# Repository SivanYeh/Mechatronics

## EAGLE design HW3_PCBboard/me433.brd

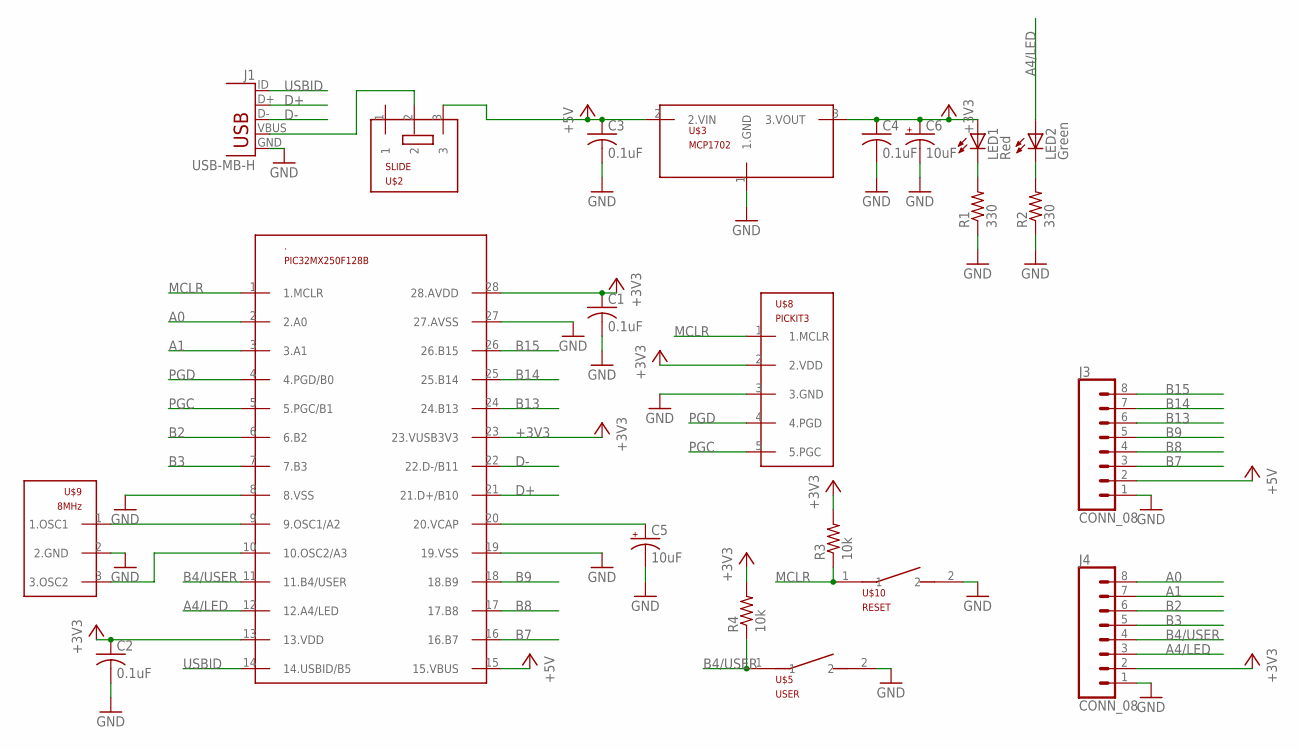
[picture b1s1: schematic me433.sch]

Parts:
.: PIC32MX250F128B; DIL28-3
C1, C2, C3, C4: 0.1uF; C025-025X050
C5, C6: 10uF; B45181B
J1: USB-MB-H
J3, J4: CONN_08; 1X08
LED1: Red; LED3MM
LED2: Green; LED3MM
R1, R2: 330; 0207/10
R3, R4: 10k; 0207/10
U$2: SLIDE
U$3: MCP1702; TO92
U$5: USER; PB
U$8: PICKIT3; 1X05
U$9: 8MHz; OSC
U$10: RESET; PB

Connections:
+3V3: ..13 (13.VDD), ..23 (23.VUSB3V3), ..28 (28.AVDD), C1.1, C2.1, C4.1, C6.+, J4.2, LED1.A, R3.2, R4.2, U$3.3 (3.VOUT), U$8.2 (2.VDD)
+5V: ..15 (15.VBUS), C3.1, J3.2, U$2.3, U$3.2 (2.VIN)
A0: ..2 (2.A0), J4.8
A1: ..3 (3.A1), J4.7
A4/LED: ..12 (12.A4/LED), J4.3, LED2.A
B2: ..6 (6.B2), J4.6
B3: ..7 (7.B3), J4.5
B4/USER: ..11 (11.B4/USER), J4.4, R4.1, U$5.1
B7: ..16 (16.B7), J3.3
B8: ..17 (17.B8), J3.4
B9: ..18 (18.B9), J3.5
B13: ..24 (24.B13), J3.6
B14: ..25 (25.B14), J3.7
B15: ..26 (26.B15), J3.8
D+: ..21 (21.D+/B10), J1.D+
D-: ..22 (22.D-/B11), J1.D-
GND: ..8 (8.VSS), ..19 (19.VSS), ..27 (27.AVSS), C1.2, C2.2, C3.2, C4.2, C5.-, C6.-, J1.GND, J3.1, J4.1, R1.1, R2.1, U$3.1 (1.GND), U$5.2, U$8.3 (3.GND), U$9.2 (2.GND), U$10.2
MCLR: ..1 (1.MCLR), R3.1, U$8.1 (1.MCLR), U$10.1
unnamed: LED2.K (C), R2.2
unnamed: ..9 (9.OSC1/A2), U$9.1 (1.OSC1)
unnamed: ..10 (10.OSC2/A3), U$9.3 (3.OSC2)
unnamed: LED1.K (C), R1.2
unnamed: ..20 (20.VCAP), C5.+
PGC: ..5 (5.PGC/B1), U$8.5 (5.PGC)
PGD: ..4 (4.PGD/B0), U$8.4 (4.PGD)
USBID: ..14 (14.USBID/B5), J1.ID
VBUS: J1.VBUS, U$2.2

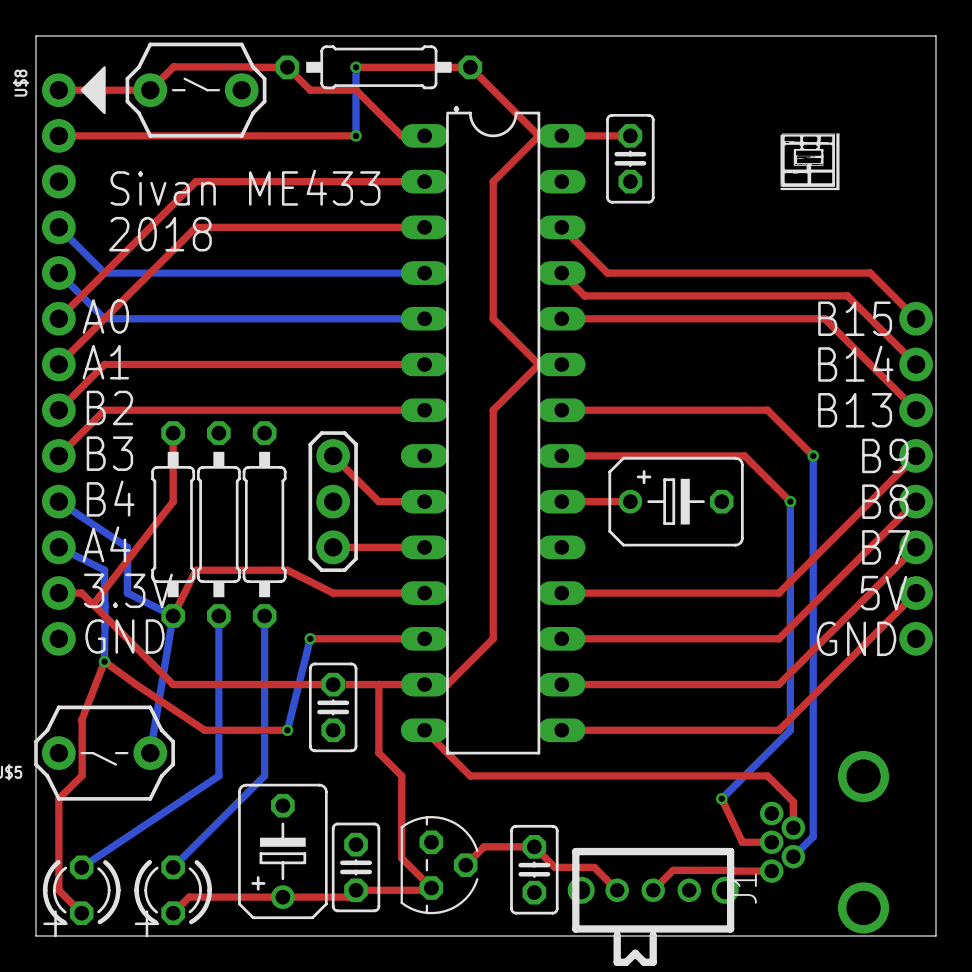
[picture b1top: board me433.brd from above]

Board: 2 copper layers, 50.0 x 50.0 mm, 22 parts (0 on the bottom side), 27 nets.

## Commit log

2018-04-12 Hw2 and circuit draft
2018-04-16 HW2 complete
2018-04-16 PCB board coming up!
2018-04-16 HW3_add1
2018-04-24 HW5_I2C
2018-04-24 HW4_SPI
2018-04-28 HW6_LCD
2018-05-03 HW_7&HW_8
2018-05-17 HW10&HW11
2018-05-23 HW12&HW13
2018-06-14 HW_14
2018-06-14 HW15
2018-06-14 HW16
2018-06-14 HW17
2018-06-14 HW18
